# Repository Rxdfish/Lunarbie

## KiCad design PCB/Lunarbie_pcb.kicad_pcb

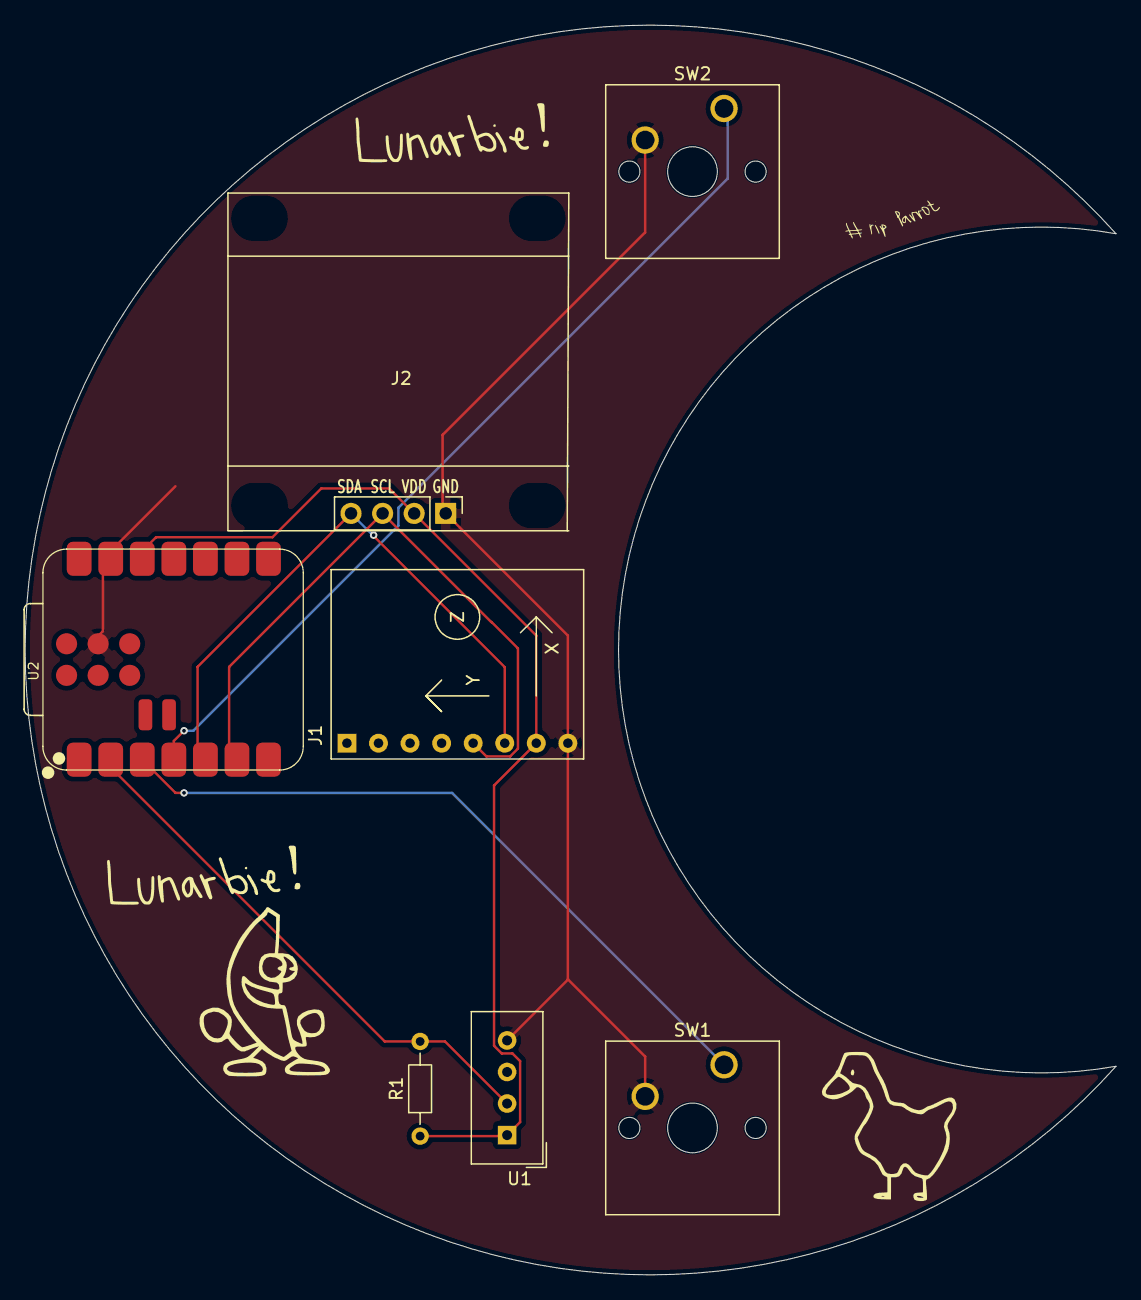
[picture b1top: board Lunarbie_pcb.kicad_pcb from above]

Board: 2 copper layers, 87.8 x 100.6 mm, 7 parts (0 on the bottom side), 7 nets.

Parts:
J1: Conn_01x08; MPU6050_Module
J2: Conn_01x04; Display_128x64_096_I2C
R1: 10k; R_Axial_DIN0204_L3.6mm_D1.6mm_P7.62mm_Horizontal
SW1, SW2: SW_Push; SW_Cherry_MX_1.00u_PCB
U1: DHT11; Aosong_DHT11_5.5x12.0_P2.54mm
U2: XIAO-ESP32-C3-SMD

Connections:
+3.3V: J1.7, J2.2, R1.1, U1.1 (VDD), U2.12 (3V3_OUT)
/DHT11 DATA: R1.2, U1.2 (DATA), U2.2 (D1)
/GPIO2: SW1.1, U2.3 (D2)
/GPIO3: SW2.1, U2.4 (D3)
/SCL: J1.6, J2.4, U2.5 (D4)
/SDA: J1.5, J2.3, U2.6 (D5)
GND: J1.8, J2.1, SW1.2, SW2.2, U1.4 (GND), U2.13 (GND), U2.18 (GND)
